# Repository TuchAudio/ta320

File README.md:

# ta320
Compact, integrated amplifier with Phono pre-amp and headphone output

## Purpose
A convenient way to monitor the output of a **Phono cartridge**. The moderate _output power_ (**~1.5 W RMS**) is enough for most uses, while a convenient **headphone output** is provided (thru 100 ohm _attenuation resistors_)

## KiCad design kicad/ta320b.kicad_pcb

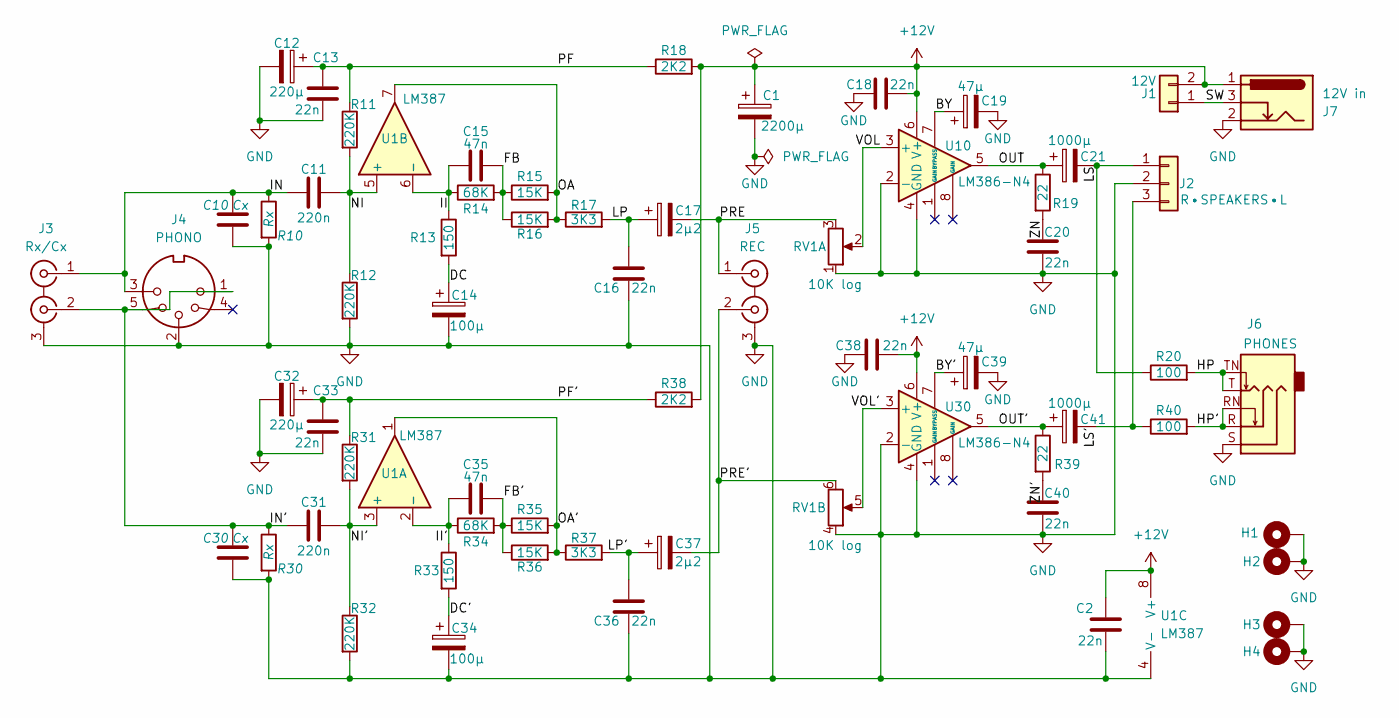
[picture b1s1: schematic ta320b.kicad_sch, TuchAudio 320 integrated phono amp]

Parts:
C1: 2200µ; CP_Radial_D13.0mm_P5.00mm
C2, C13, C18, C20, C33, C38, C40: 22n; C_Disc_D6.0mm_W2.5mm_P5.00mm
C10, C30: Cx; PinSocket_1x02_P2.54mm_Vertical
C11, C31: 220n; C_Rect_L7.2mm_W3.0mm_P5.00mm_FKS2_FKP2_MKS2_MKP2
C12, C32: 220µ; CP_Radial_D6.3mm_P2.50mm
C14, C34: 100µ; CP_Radial_D4.0mm_P1.50mm
C15, C35: 47n; C_Rect_L7.2mm_W2.5mm_P5.00mm_FKS2_FKP2_MKS2_MKP2
C16, C36: 22n; C_Rect_L7.2mm_W2.5mm_P5.00mm_FKS2_FKP2_MKS2_MKP2
C17, C37: 2µ2; CP_Radial_D4.0mm_P1.50mm
C19, C39: 47µ; CP_Radial_D4.0mm_P1.50mm
C21, C41: 1000µ; CP_Radial_D10.0mm_P5.00mm
H1, H2, H3, H4: MountingHole_Pad; MountingHole_3.2mm_M3_DIN965_Pad
J1: 12V; JST_EH_S2B-EH_1x02_P2.50mm_Horizontal
J2: R•SPEAKERS•L; TerminalBlock_MaiXu_MX126-5.0-03P_1x03_P5.00mm
J3: Rx/Cx; 2xRCA_vertical
J4: PHONO; DIN 5-180deg
J5: REC; 2xRCA_vertical
J6: PHONES; Jack_3.5mm_CUI_SJ1-3525N_Horizontal
J7: 12V in; BarrelJack_GCT_DCJ200-10-A_Horizontal
R10, R30: Rx; PinSocket_1x02_P2.54mm_Vertical
R11, R12, R31, R32: 220K; R_Axial_DIN0207_L6.3mm_D2.5mm_P10.16mm_Horizontal
R13, R33: 150; R_Axial_DIN0207_L6.3mm_D2.5mm_P10.16mm_Horizontal
R14, R34: 68K; R_Axial_DIN0207_L6.3mm_D2.5mm_P10.16mm_Horizontal
R15, R16, R35, R36: 15K; R_Axial_DIN0207_L6.3mm_D2.5mm_P10.16mm_Horizontal
R17, R37: 3K3; R_Axial_DIN0207_L6.3mm_D2.5mm_P10.16mm_Horizontal
R18, R38: 2K2; R_Axial_DIN0207_L6.3mm_D2.5mm_P10.16mm_Horizontal
R19, R39: 22; R_Axial_DIN0207_L6.3mm_D2.5mm_P10.16mm_Horizontal
R20, R40: 100; R_Axial_DIN0207_L6.3mm_D2.5mm_P10.16mm_Horizontal
RV1: 10K log; Potentiometer_Alps_225G_Dual_Horizontal
U1: LM387; DIP-8_W7.62mm
U10, U30: LM386-N4; DIP-8_W7.62mm

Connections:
+12V: C1.1, C2.2, C18.2, C38.2, J1.2, J7.1, R18.2, R38.2, U1.8 (V+), U10.6 (V+), U30.6 (V+)
/BY: C19.1, U10.7 (BYPASS)
/BY': C39.1, U30.7 (BYPASS)
/DC: C14.1, R13.2
/DC': C34.1, R33.2
/FB: C15.2, R14.2, R15.1, R16.1
/FB': C35.2, R34.2, R35.1, R36.1
/HP: J6.T, J6.TN, R20.2
/HP': J6.R, J6.RN, R40.2
/II: C15.1, R13.1, R14.1, U1.6 (-)
/II': C35.1, R33.1, R34.1, U1.2 (-)
/IN: C10.1, C11.1, J3.1 (IN1), J4.3, R10.1
/IN': C30.1, C31.1, J3.2 (IN2), J4.1, J4.5, R30.1
/LP: C16.2, C17.1, R17.2
/LP': C36.2, C37.1, R37.2
/LS: C21.2, J2.1, R20.1
/LS': C41.2, J2.3, R40.1
/NI: C11.2, R11.2, R12.1, U1.5 (+)
/NI': C31.2, R31.2, R32.1, U1.3 (+)
/OA: R15.2, R16.2, R17.1, U1.7
/OA': R35.2, R36.2, R37.1, U1.1
/OUT: C21.1, R19.1, U10.5
/OUT': C41.1, R39.1, U30.5
/PF: C12.1, C13.2, R11.1, R18.1
/PF': C32.1, C33.2, R31.1, R38.1
/PRE: C17.2, J5.1 (IN1), RV1.3
/PRE': C37.2, J5.2 (IN2), RV1.6
/SW: J1.1, J7.3
/VOL: RV1.2, U10.3 (+)
/VOL': RV1.5, U30.3 (+)
/ZN: C20.1, R19.2
/ZN': C40.1, R39.2
GND: C1.2, C2.1, C10.2, C12.2, C13.1, C14.2, C16.1, C18.1, C19.2, C20.2, C30.2, C32.2, C33.1, C34.2, C36.1, C38.1, C39.2, C40.2, H1.1, H2.1, H3.1, H4.1, J2.2, J3.3 (EXT), J4.2, J5.3 (EXT), J6.S, J7.2, R10.2, R12.2, R30.2, R32.2, RV1.1, RV1.4, U1.4 (V-), U10.2 (-), U10.4 (GND), U30.2 (-), U30.4 (GND)

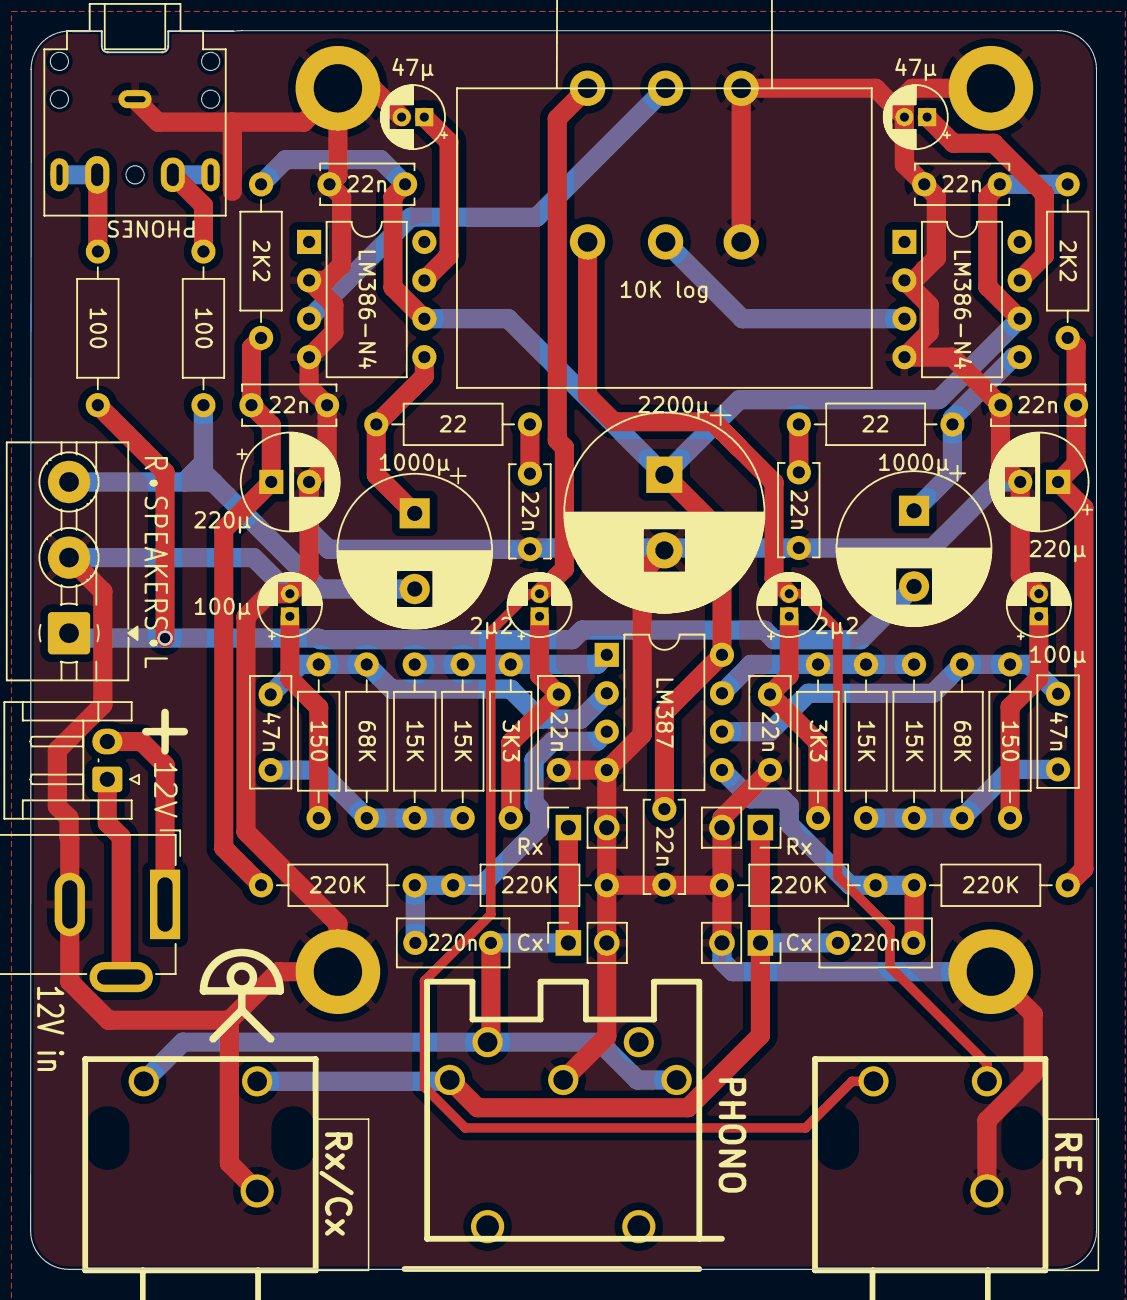
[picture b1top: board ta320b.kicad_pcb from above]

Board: 2 copper layers, 70.4 x 81.8 mm, 63 parts (0 on the bottom side), 33 nets.

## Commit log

2025-11-08 add KiCAD files
2025-11-12 purpose
2025-11-12 add pics
